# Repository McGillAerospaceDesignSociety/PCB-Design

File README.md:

# Small-BEC
This is a very small and simple BEC based on the Onsemi MC33269. It is intended to readily provide regulated power from a battery during electronic prototyping or UAS assembly. As the MC33269 is available in 3.3V / 5V / 12V output versions, only one PCB design is needed.

## Electrical Characterstics
The following table summarizes some basic characterstics of MC33269

| Symbol | Description | Value |
|--------------|---------------------|-----------------------------|
| V_in | Voltage Input (Max) | 20V |
| V_out | Voltage Output | 3.3V / 5V / 12V |
| I_limit | Current Limit | 800mA |
| V_in - V_out | Dropout Voltage | 1.1 - 1.35V at 800mA output |

## Pictures
Schematics

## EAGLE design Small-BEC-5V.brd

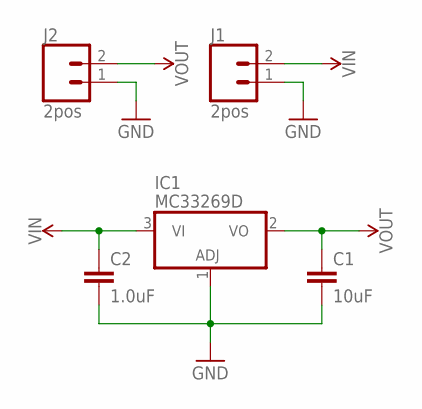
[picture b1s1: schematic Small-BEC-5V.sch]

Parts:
C1: 10uF; 0805
C2: 1.0uF; 0805
IC1: MC33269D; DPACK
J1, J2: 2pos; 1X02

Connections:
GND: C1.2, C2.2, IC1.1 (ADJ), J1.1, J2.1
VIN: C2.1, IC1.3 (VI), J1.2
VOUT: C1.1, IC1.2 (VO), J2.2

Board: 2 copper layers, 5 parts (0 on the bottom side), 3 nets, no tracks yet.

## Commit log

2019-02-06 Add EAGLE designs
2019-02-06 Add Graphics
2019-02-06 rename

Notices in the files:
parts and their libraries:
SparkFun-Capacitors: Licensing: Creative Commons ShareAlike 4.0 International - https://creativecommons.org/licenses/by-sa/4.0
